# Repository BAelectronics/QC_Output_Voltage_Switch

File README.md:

[Kapcsolódó videó / Related video](https://youtu.be/jLJ_5dmPatM)

The language of the video is Hungarian, but English subtitles are available.

# USB gyorstöltő kimenő feszültségét beállító eszköz (5/9/12V)
A videóban bemutatott és a projekthez tartozó fájlok, rajzok, kódok stb. megtalálhatóak ezen az oldalon.

A vezérlőpanel kapcsolása és nyákterve KiCad 5.1 programmal készült.

Ezzel a kis adapterrel egyszerűen lehet módosítani egy Quick Charge 2.0 vagy 3.0 képes USB-s gyorstöltő kimenő feszültségét csupán egy ATtiny13A MCU-val és néhány egyéb alkatrésszel. A hardver egyféle, azonban 2 eltérő működésű szoftver van fejlesztve, hogy ha valaki utánépítené akkor ki tudja választani a számára szimpatikus módot. Természetesen lehet kombinálni is vagy másfajta működést kitalálni ha van hozzá affinitásod.

### MODE 1 képességek
- +gomb --> feszültség növelése +0,2Volttal
- -gomb --> feszültség csökkentése -0,2Volttal
- Mindkét gombot egyszerre lenyomva --> 5V beállítás

### MODE 2 képességek
- +gomb --> ugrás 9Voltra 5Voltról vagy 12Voltra 9Voltról
- -gomb --> ugrás 9Voltra 12Voltról vagy 5Voltra 9Voltról
- Egyiket nyomvatartva és megnyomva a másikat --> beállított feszültség mentése EEPROM-ba, következő indításnál magától betöltődik

# USB Quick Charge output voltage switch device (5/9/12V)
You can find here files, schematics, codes, etc. Everything what presented in the video and associated with the project.

The control board schematic and PCB designed with KiCad 5.1.

With this small adapter, you can easily adjust the output voltage of a Quick Charge 2.0 or 3.0 capable USB charger with only an ATtiny13A MCU and few parts. The hardware is one, but the software has 2 different mode, so if you want to rebuild, then you can choose the mode they like. Of course, you can also combine or develop new with a different kind of action if you have an affinity for it.

### MODE 1 features
- +button --> increase the Voltage +0,2V
- -button --> decrease the Voltage -0,2V
- Both button pressed at the same time --> set 5V

### MODE 2 features
- +button --> jump to 9V from 5V or jump to 12V from 9V
- -button --> jump to 9V from 12V or jump to 5V from 9V
- One button hold and press the other --> save set Voltage to the EEPROM (next start auto load)

The device:

Thanks to them:
- [Hugatry's HackVlog](https://www.youtube.com/channel/UCHgeChD442K0ah-KxEg0PHw) He came up with the idea and first code to control QC2. 
- [QC2Control](https://github.com/septillion-git/QC2Control) Timo Engelgeer (Septillion) who made a nice wrapper for QC2.
- [QC3Control](https://github.com/vdeconinck/QC3Control) He is the latest developer of the idea for QC3.

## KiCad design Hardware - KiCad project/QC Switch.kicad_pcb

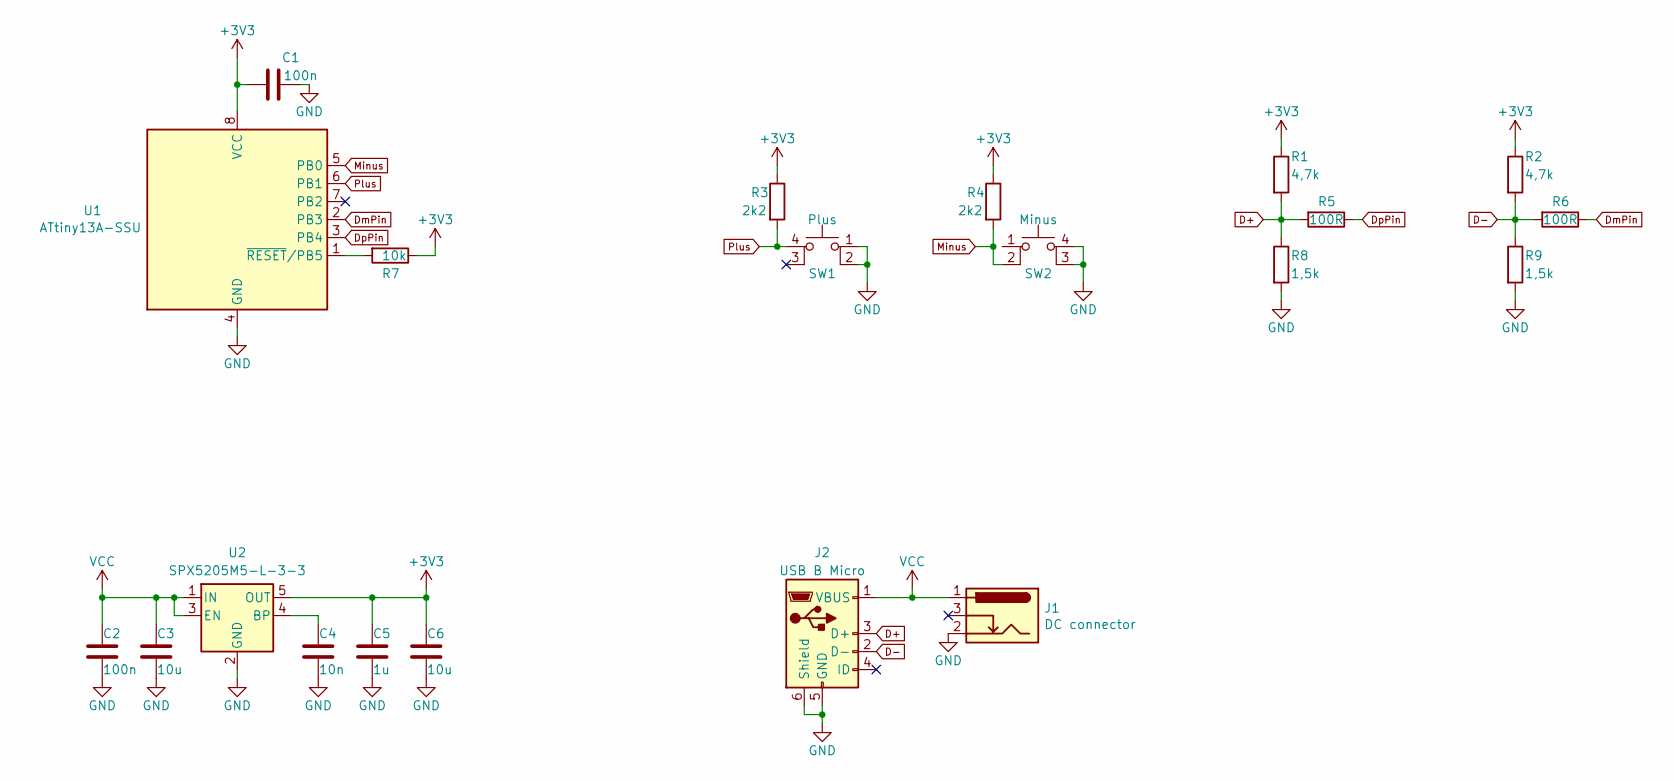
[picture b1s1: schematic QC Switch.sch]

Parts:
C1, C2: 100n; C_0805_2012Metric
C3, C6: 10u; C_0805_2012Metric
C4: 10n; C_0805_2012Metric
C5: 1u; C_0805_2012Metric
J1: DC connector; BarrelJack_Horizontal
J2: USB B Micro; USB_Micro-B_Amphenol_10104110_Horizontal
R1, R2: 4,7k; R_0805_2012Metric
R3, R4: 2k2; R_0805_2012Metric
R5, R6: 100R; R_0805_2012Metric
R7: 10k; R_0805_2012Metric
R8, R9: 1,5k; R_0805_2012Metric
SW1: Plus; SW_TH_Tactile_Omron_B3F-10xx
SW2: Minus; SW_TH_Tactile_Omron_B3F-10xx
U1: ATtiny13A-SSU; SOIC-8_3.9x4.9mm_P1.27mm
U2: SPX5205M5-L-3-3; SOT-23-5

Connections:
+3V3: C1.1, C5.1, C6.1, R1.1, R2.1, R3.1, R4.1, R7.1, U1.8 (VCC), U2.5 (OUT)
D+: J2.3 (D+), R1.2, R5.2, R8.1
D-: J2.2 (D-), R2.2, R6.2, R9.1
DmPin: R6.1, U1.2 (PB3)
DpPin: R5.1, U1.3 (PB4)
GND: C1.2, C2.2, C3.2, C4.2, C5.2, C6.2, J1.2, J2.5 (GND), J2.6 (Shield), R8.2, R9.2, SW1.1, SW1.2, SW2.3 (K), SW2.4 (A), U1.4 (GND), U2.2 (GND)
Minus: R4.2, SW2.2, U1.5 (PB0)
unnamed: C4.1, U2.4 (BP)
unnamed: R7.2, U1.1 (~RESET~/PB5)
Plus: R3.2, SW1.4 (A), U1.6 (PB1)
VCC: C2.1, C3.1, J1.1, J2.1 (VBUS), U2.1 (IN), U2.3 (EN)

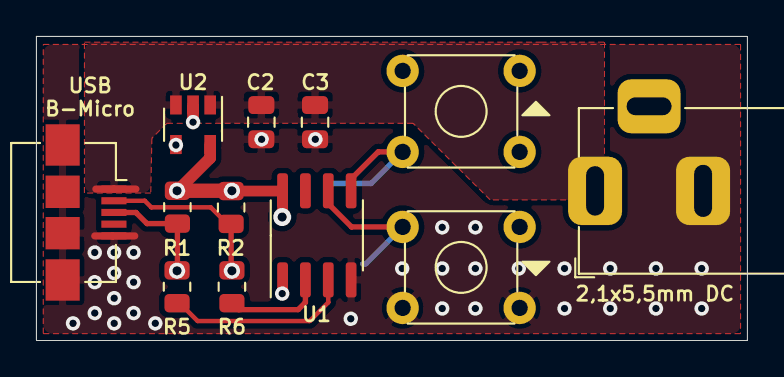
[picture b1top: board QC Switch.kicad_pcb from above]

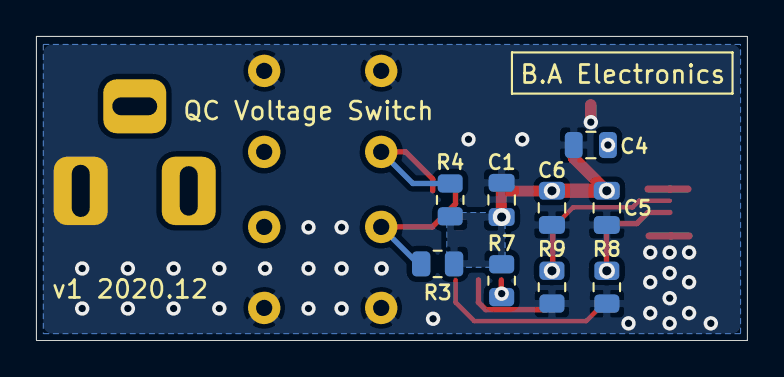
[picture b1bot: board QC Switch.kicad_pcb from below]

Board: 2 copper layers, 39.5 x 16.9 mm, 21 parts (9 on the bottom side), 11 nets.
